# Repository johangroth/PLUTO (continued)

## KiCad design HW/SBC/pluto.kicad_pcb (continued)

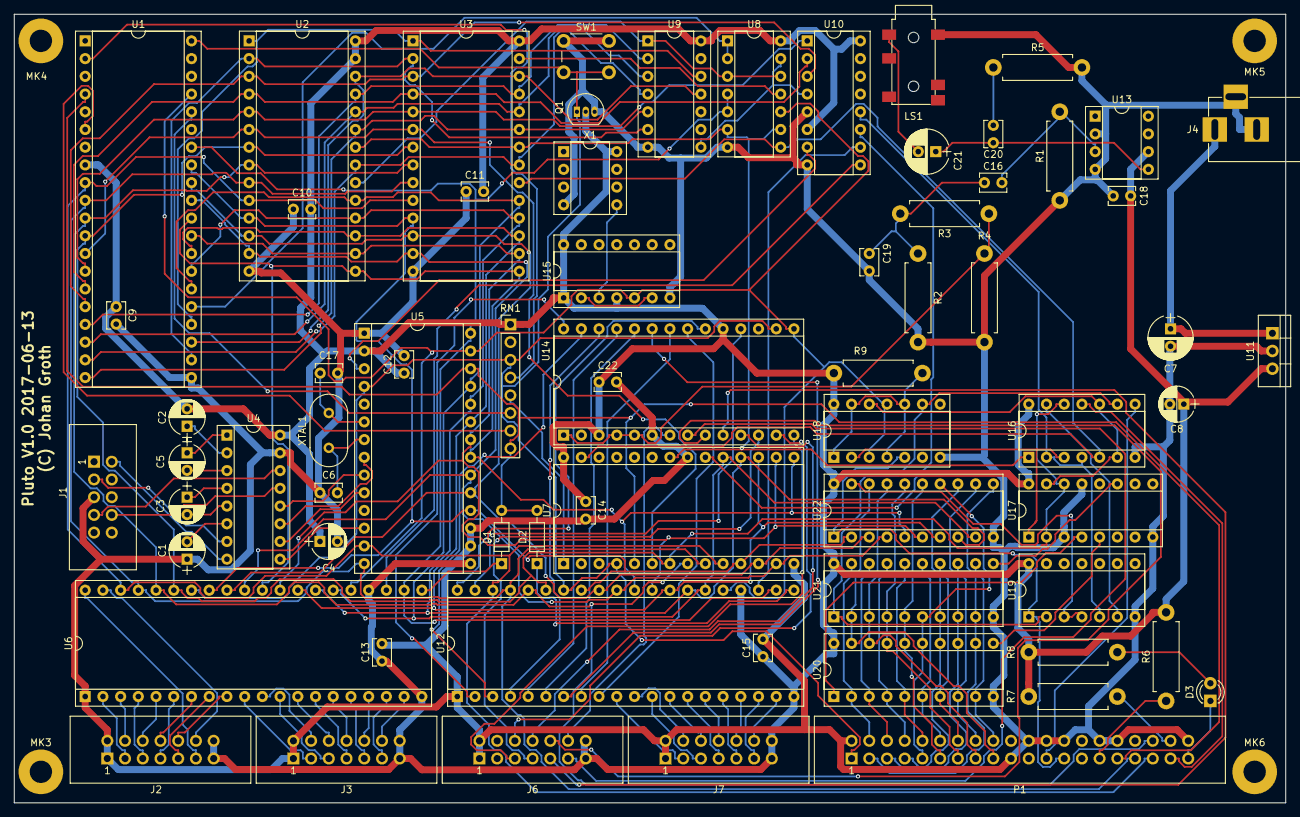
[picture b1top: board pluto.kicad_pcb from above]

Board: 2 copper layers, 182.2 x 113.0 mm, 73 parts (0 on the bottom side), 151 nets.

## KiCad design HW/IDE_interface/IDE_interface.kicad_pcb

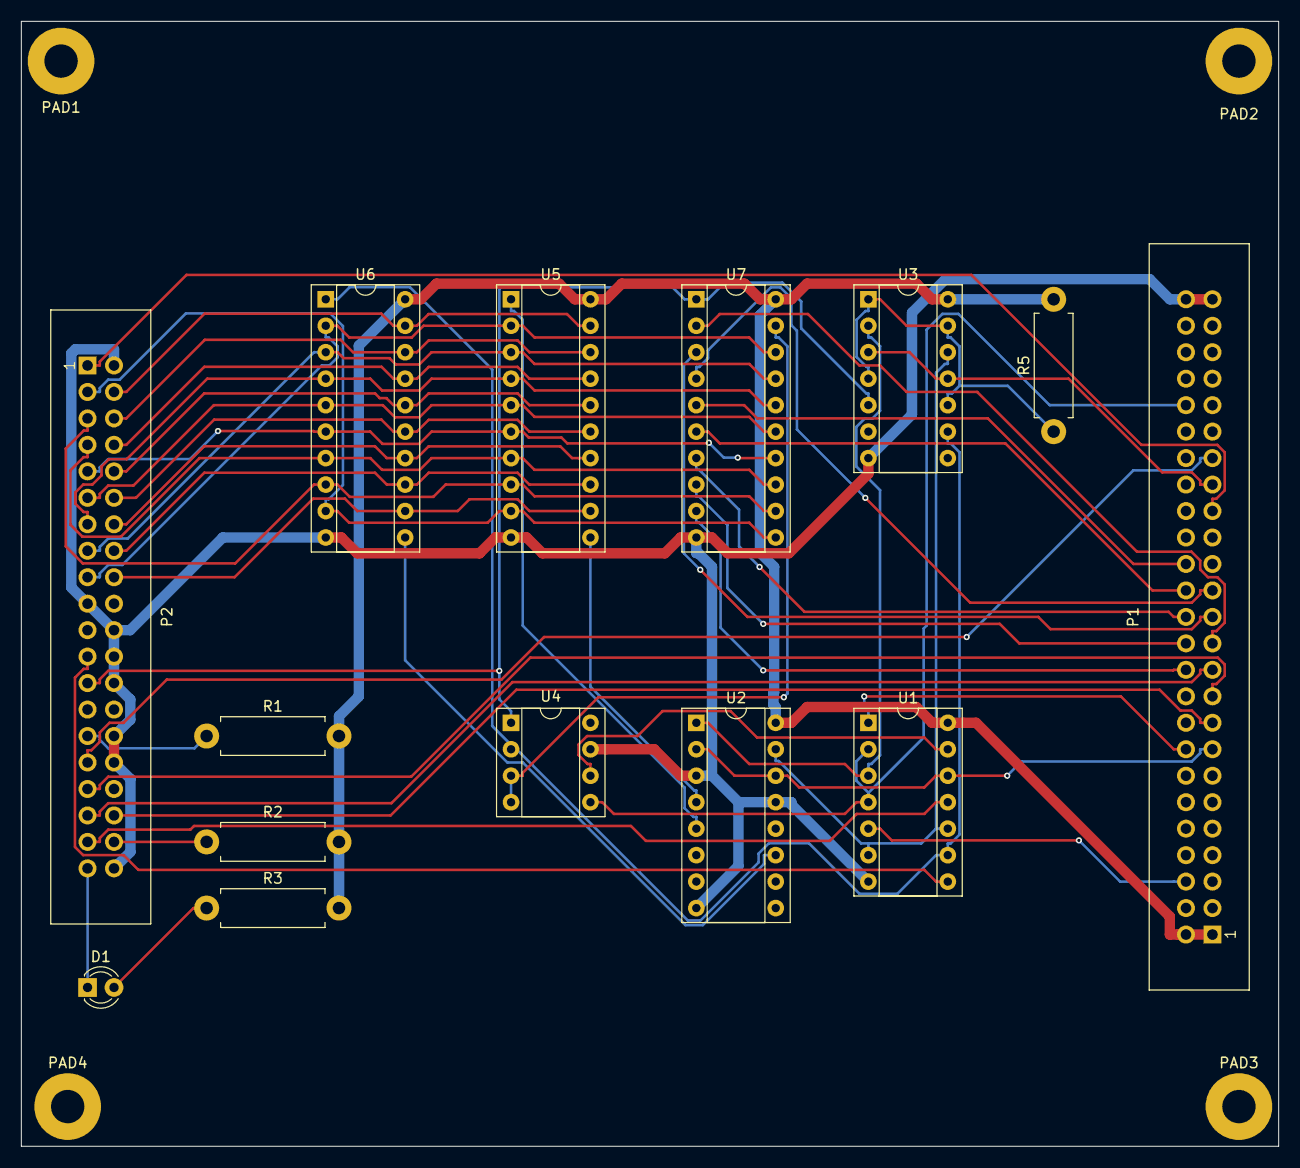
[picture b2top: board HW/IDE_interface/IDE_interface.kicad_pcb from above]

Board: 2 copper layers, 120.7 x 108.0 mm, 18 parts (0 on the bottom side), 52 nets.

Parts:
D1: LED; LED_D3.0mm
P1: EXPANSION PORT; IDC_Header_Straight_50pins
P2: IDE0; IDC_Header_Straight_40pins
PAD1, PAD2, PAD3, PAD4: MountingHole_3.2mm_M3_Pad
R1: 3.3K; R_Axial_DIN0411_L9.9mm_D3.6mm_P12.70mm_Horizontal
R2, R3: 1K; R_Axial_DIN0411_L9.9mm_D3.6mm_P12.70mm_Horizontal
R5: 1k; R_Axial_DIN0411_L9.9mm_D3.6mm_P12.70mm_Horizontal
U1: 74LS32; DIP-14_W7.62mm_Socket
U2: 74LS139; DIP-16_W7.62mm_Socket
U3: 74HC74; DIP-14_W7.62mm_Socket
U4: 74LS08; DIP-8_W7.62mm_Socket
U5, U6: 74LS574; DIP-20_W7.62mm_Socket
U7: 74HC245; DIP-20_W7.62mm_Socket

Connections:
/A0: P1.21, P2.35
/A1: P1.19, P2.33
/A2: P1.17, P2.36
/A3: P1.15, U1.12, U2.2, U2.14
/CLK2: P1.35, U3.3, U3.11
/D0: P1.23, U7.2
/D1: P1.25, U7.3
/D2: P1.27, U7.4
/D3: P1.30, U7.5
/D4: P1.28, U7.6
/D5: P1.26, U7.7
/D6: P1.24, U7.8
/D7: P1.22, U7.9
/IDE-D0: P2.17, U5.2, U6.2, U7.18
/IDE-D1: P2.15, U5.3, U6.3, U7.17
/IDE-D2: P2.13, U5.4, U6.4, U7.16
/IDE-D3: P2.11, U5.5, U6.5, U7.15
/IDE-D4: P2.9, U5.6, U6.6, U7.14
/IDE-D5: P2.7, U5.7, U6.7, U7.13
/IDE-D6: P2.5, U5.8, U6.8, U7.12
/IDE-D7: P2.3, U5.9, U6.9, U7.11
/IDE-D8: P2.4, U5.19, U6.19
/IDE-D9: P2.6, U5.18, U6.18
/IDE-D10: P2.8, U5.17, U6.17
/IDE-D11: P2.10, U5.16, U6.16
/IDE-D12: P2.12, U5.15, U6.15
/IDE-D13: P2.14, U5.14, U6.14
/IDE-D14: P2.16, U5.13, U6.13
/IDE-D15: P2.18, U5.12, U6.12
/~7F8X: P1.42, U1.2, U1.4, U4.5
/~DIOR: P2.25, U3.5, U4.1, U7.1
/~DIOW: P2.23, U1.8
/~IDE:CS0: P2.37, U1.11
/~IDE:CS1: P2.38, R2.1
/~IDE:DASP: D1.1, P2.39
/~IDE:DMACK: P2.29, R1.1
/~IRQ: P1.37, P2.31
/~MRD: P1.16, U1.1
/~MWR: P1.6, U1.5
/~RES: P1.33, P2.1
GND: P1.49, P1.50, P2.2, P2.19, P2.22, P2.24, P2.26, P2.30, P2.32, P2.40, U1.7, U2.3, U2.8, U2.13, U3.7, U4.7, U5.10, U6.10, U7.10
unnamed: D1.2, R3.1
unnamed: R5.1, U3.1, U3.4, U3.10, U3.13
unnamed: U1.3, U2.1, U3.2
unnamed: U1.9, U3.9, U4.2, U6.1
unnamed: U1.6, U1.10, U2.15, U3.12
unnamed: U1.13, U4.6
unnamed: U2.4, U5.11
unnamed: U2.5, U5.1
unnamed: U2.11, U6.11
unnamed: U4.3, U4.4, U7.19
VCC: P1.1, P1.2, R1.2, R2.2, R3.2, R5.2, U1.14, U2.16, U3.14, U5.20, U6.20, U7.20

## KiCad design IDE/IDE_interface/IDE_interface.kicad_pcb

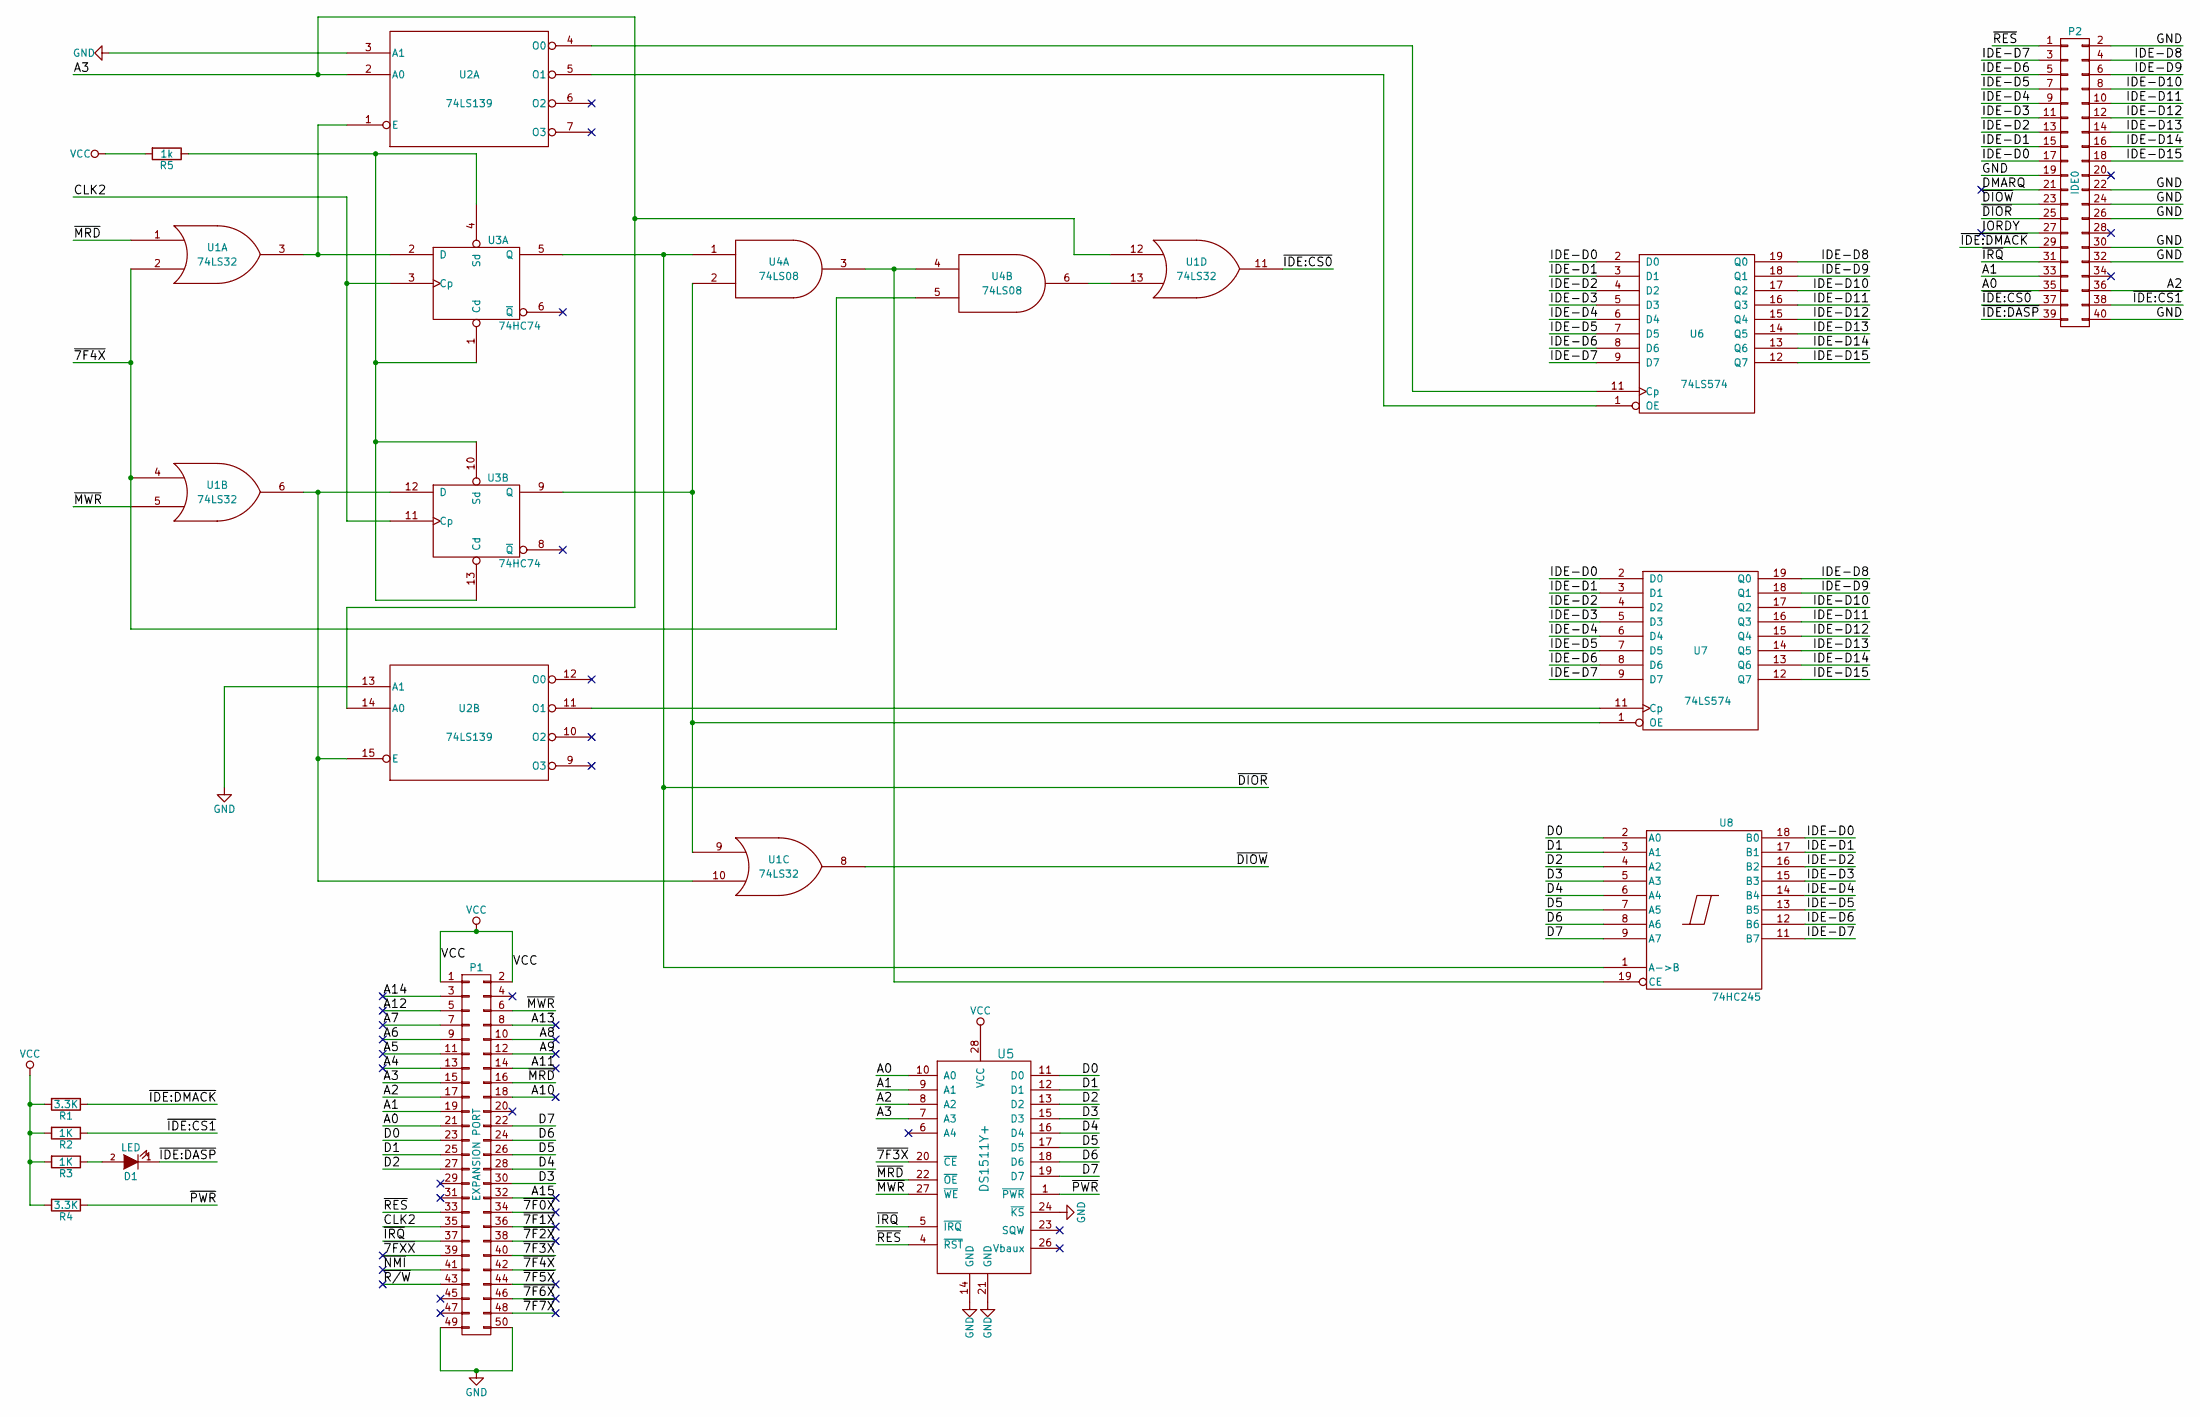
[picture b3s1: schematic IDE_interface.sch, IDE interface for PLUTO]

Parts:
D1: LED; LED-3MM
P1: EXPANSION PORT; Pin_Header_Straight_2x25
P2: IDE0; Pin_Header_Straight_2x20
R1, R4: 3.3K; Resistor_Horizontal_RM7mm
R2, R3: 1K; Resistor_Horizontal_RM7mm
R5: 1k; Resistor_Horizontal_RM7mm
U1: 74LS32; DIP-14_W7.62mm
U2: 74LS139; DIP-16_W7.62mm
U3: 74HC74; DIP-14_W7.62mm
U4: 74LS08; DIP-8_W7.62mm
U5: DS1511Y+; DIP-28_W15.24mm
U6, U7: 74LS574; DIP-20_W7.62mm
U8: 74HC245; DIP-20_W7.62mm

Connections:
/A0: P1.21, P2.35, U5.10 (A0)
/A1: P1.19, P2.33, U5.9 (A1)
/A2: P1.17, P2.36, U5.8 (A2)
/A3: P1.15, U1.12, U2.2 (A0), U2.14 (A0), U5.7 (A3)
/A4: P1.13
/A5: P1.11
/A6: P1.9
/A7: P1.7
/A8: P1.10
/A9: P1.12
/A10: P1.18
/A11: P1.14
/A12: P1.5
/A13: P1.8
/A14: P1.3
/A15: P1.32
/CLK2: P1.35, U3.3 (Cp), U3.11 (Cp)
/D0: P1.23, U5.11 (D0), U8.2 (A0)
/D1: P1.25, U5.12 (D1), U8.3 (A1)
/D2: P1.27, U5.13 (D2), U8.4 (A2)
/D3: P1.30, U5.15 (D3), U8.5 (A3)
/D4: P1.28, U5.16 (D4), U8.6 (A4)
/D5: P1.26, U5.17 (D5), U8.7 (A5)
/D6: P1.24, U5.18 (D6), U8.8 (A6)
/D7: P1.22, U5.19 (D7), U8.9 (A7)
/DMARQ: P2.21
/IDE-D0: P2.17, U6.2 (D0), U7.2 (D0), U8.18 (B0)
/IDE-D1: P2.15, U6.3 (D1), U7.3 (D1), U8.17 (B1)
/IDE-D2: P2.13, U6.4 (D2), U7.4 (D2), U8.16 (B2)
/IDE-D3: P2.11, U6.5 (D3), U7.5 (D3), U8.15 (B3)
/IDE-D4: P2.9, U6.6 (D4), U7.6 (D4), U8.14 (B4)
/IDE-D5: P2.7, U6.7 (D5), U7.7 (D5), U8.13 (B5)
/IDE-D6: P2.5, U6.8 (D6), U7.8 (D6), U8.12 (B6)
/IDE-D7: P2.3, U6.9 (D7), U7.9 (D7), U8.11 (B7)
/IDE-D8: P2.4, U6.19 (Q0), U7.19 (Q0)
/IDE-D9: P2.6, U6.18 (Q1), U7.18 (Q1)
/IDE-D10: P2.8, U6.17 (Q2), U7.17 (Q2)
/IDE-D11: P2.10, U6.16 (Q3), U7.16 (Q3)
/IDE-D12: P2.12, U6.15 (Q4), U7.15 (Q4)
/IDE-D13: P2.14, U6.14 (Q5), U7.14 (Q5)
/IDE-D14: P2.16, U6.13 (Q6), U7.13 (Q6)
/IDE-D15: P2.18, U6.12 (Q7), U7.12 (Q7)
/IORDY: P2.27
/~7F0X: P1.34
/~7F1X: P1.36
/~7F2X: P1.38
/~7F3X: P1.40, U5.20 (~CE)
/~7F4X: P1.42, U1.2, U1.4, U4.5
/~7F5X: P1.44
/~7F6X: P1.46
/~7F7X: P1.48
/~7FXX: P1.39
/~DIOR: P2.25, U3.5 (Q), U4.1, U8.1 (A->B)
/~DIOW: P2.23, U1.8
/~IDE:CS0: P2.37, U1.11
/~IDE:CS1: P2.38, R2.1
/~IDE:DASP: D1.1 (K), P2.39
/~IDE:DMACK: P2.29, R1.1
/~IRQ: P1.37, P2.31, U5.5 (~IRQ)
/~MRD: P1.16, U1.1, U5.22 (~OE)
/~MWR: P1.6, U1.5, U5.27 (~WE)
/~NMI: P1.41
/~PWR: R4.1, U5.1 (~PWR)
/~R/W: P1.43
/~RES: P1.33, P2.1, U5.4 (~RST)
GND: P1.49, P1.50, P2.2, P2.19, P2.22, P2.24, P2.26, P2.30, P2.32, P2.40, U1.7 (GND), U2.3 (A1), U2.8 (GND), U2.13 (A1), U3.7 (GND), U4.7 (GND), U5.14 (GND), U5.21 (GND), U5.24 (~KS), U6.10 (GND), U7.10 (GND), U8.10 (GND)
unnamed: D1.2 (A), R3.1
unnamed: R5.1, U3.1 (Cd), U3.4 (Sd), U3.10 (Sd), U3.13 (Cd)
unnamed: U1.3, U2.1 (E), U3.2 (D)
unnamed: U1.9, U3.9 (Q), U4.2, U7.1 (OE)
unnamed: U1.6, U1.10, U2.15 (E), U3.12 (D)
unnamed: U1.13, U4.6
unnamed: U2.4 (O0), U6.11 (Cp)
unnamed: U2.5 (O1), U6.1 (OE)
unnamed: U2.11 (O1), U7.11 (Cp)
unnamed: U4.3, U4.4, U8.19 (CE)
VCC: P1.1, P1.2, R1.2, R2.2, R3.2, R4.2, R5.2, U1.14 (VCC), U2.16 (VCC), U3.14 (VCC), U5.28 (VCC), U6.20 (VCC), U7.20 (VCC), U8.20 (VCC)

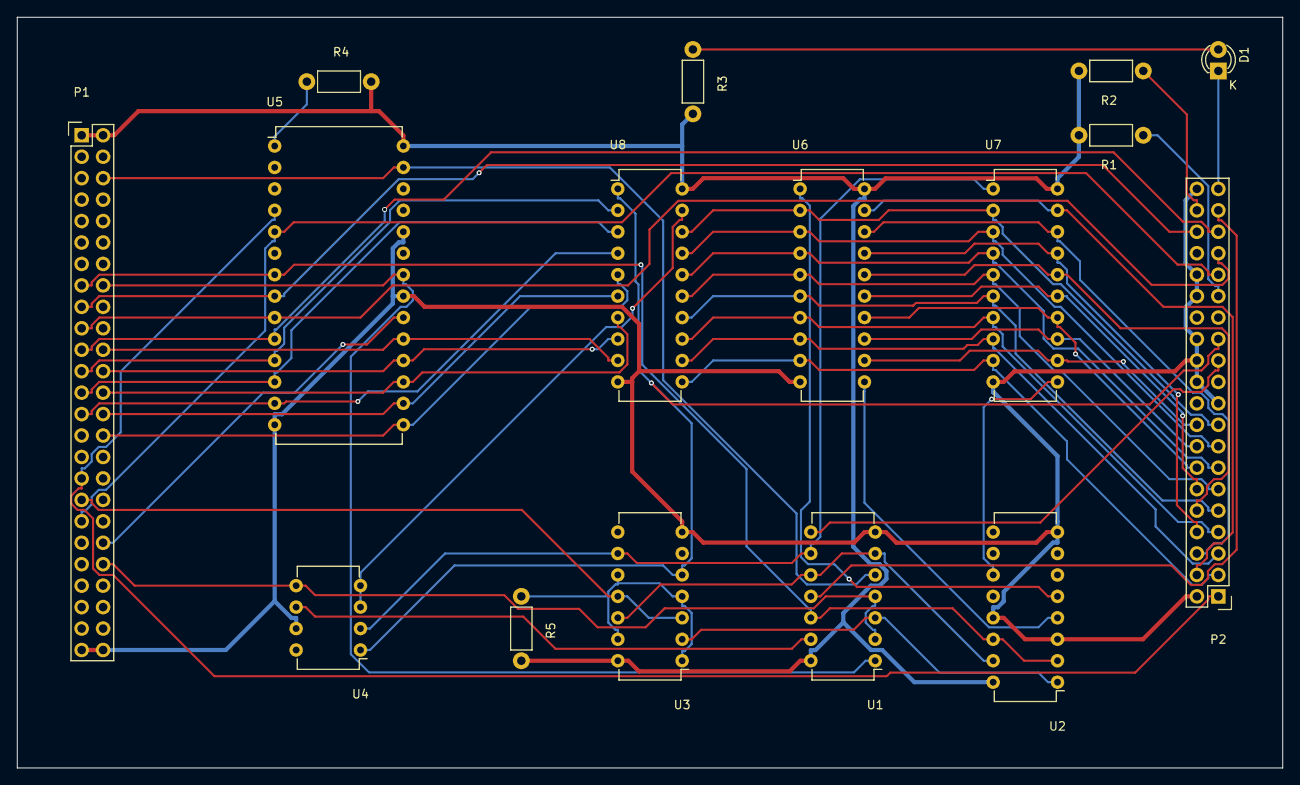
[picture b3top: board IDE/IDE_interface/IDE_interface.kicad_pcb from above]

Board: 2 copper layers, 149.9 x 88.9 mm, 16 parts (0 on the bottom side), 54 nets.

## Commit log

2016-09-28 Updated PROMPT to handle large messages.
2016-09-29 Added a lot of documentation
2016-09-29 Minor updates to docs.
2016-09-29 Correction of spelling mistakes, wording etc
2016-10-01 Updates to goals
2016-10-07 Added datasheets for IDE interface. TaliForth source added. KiCad documentation added. Some ide assembler routines added (not tested). VT100 escape sequences added.
2016-10-12 Added escape seq for colours. Adjusted ram size for Tali Forth
2016-10-27 Removed hardcoded addresses to subroutines printed out by Q command. Added prototype for an IDE driver. Added datasheets for RTC.
2016-11-21 Use 65C20 mnemonics
2016-12-04 Added datasheet for CDP 65C51.
2016-12-04 Corrected spelling mistakes.
2016-12-08 Added Daryl Rictor's XModem implementation instead of SyMonIII upload/download subroutines.
2016-12-08 Using SyMonIII subroutines in xmodem.asm.
2016-12-12 Integration of XMODEM/CRC with SyMonIII
2017-02-14 New version of Tali Forth
2017-02-14 Added TaliForth
2017-02-14 Added IDE interface schema
2017-02-15 Initialisation of VIA. Added emacs TAGS to SyMonIII.
2017-02-15 remove never used schematics.
2017-02-15 Deleted TaliForth
2017-02-15 Added TaliForth without .git directory
2017-02-18 Move ide routines to SyMonII. Small updates to xmodem. Tagged all asm files.
2017-02-18 Added TAGS to Tali Forth. Small updates to xmodem.asm
2017-02-21 Moved all assembler files to one directory.
2017-02-21 Tali kernel removed from assembly chain.
2017-02-21 Beginning of a init routine for IDE.
2017-02-22 Removed seldom used commands in kernel. Clean up of Forth.
2017-02-22 Added cfs documentation.
2017-02-22 Indentation changes.
2017-02-22 CFS documentation. Perhaps move to its own file.
2017-02-22 All available CFS documentation added.
2017-02-23 Finished doc for CFS.
2017-02-23 Basic ide has two ZP var d and e. Hangover from Z-80 port. Check original what is going on there. cfs calls read sector as a test. Main calls cfs as a test.
2017-02-23 Cleanup of comments in cfs.asm. Started a Zero Page variable list for use of all asm files.
2017-02-24 Updates tags files. Embroy to Makefile added.
2017-02-26 Added forth vi and asm from Durexforth.
2017-02-26 chmodded vi.fs
2017-03-07 Removed TaliForth
2017-03-14 vt100 control sequences.
2017-03-23 Revised the memory map. I/O blocks are now 32 bytes.
2017-03-23 Updates to IDE interface.
2017-03-23 Added vt100 terminal code and schematics for PLUTO SBC board.
2017-03-24 Changed names of IO select lines.
2017-03-24 Renamed IDE directory to HW
2017-03-24 Started to make the schematics for pluto main board using multiple sheets.
2017-03-25 PLUTO SBC with RTC schematics done.
2017-03-25 Via connectors.pro? Commited and pushed just in case.
2017-03-25 The PCB layout editor doesn't like 7805's footprint.
2017-03-25 Removed old Pluto schematics.
2017-03-25 Renamed multisheet schematics to SBC
2017-03-26 Some changes to the schematics.
2017-03-27 Updated test with new address for VIA. Updated doc with VIA details.
2017-03-28 Added a couple of procedure assembler directives. ctags file added
2017-03-28 Connected all relevant I/O select signals to expansion port.
2017-03-29 Corrected some Z80 -> 65C02 errors.
2017-03-29 Added some comments.
2017-03-29 New indentaion.
2017-03-30 Removed duplicated options in asmpluto.sh.
2017-03-31 Downloaded the orginal version of SyMonIII.
2017-03-31 Removed Tali Forth as it is going to be rewritten when Liara Forth is in Beta.
2017-04-03 New MB design. Includes RTC. New IDE design.
2017-04-04 Added DS1511 code. Code in 65816 assembler so conversion is needed.
2017-04-19 Added original xmodem code some datasheets and a C02Monitor.
2017-04-19 Fixed pluto kernel (SyMon, command address table had been corrupted).
2017-04-20 Tab clean up. Rewrite of Flush in xmodem.asm.
2017-04-20 Include xmodem in the assembly list.
2017-04-25 Removed xmodem from main.asm. Xmodem seem to disrupt serial communication. Disabled upload/download in kernel.
2017-04-25 Ignore .rom files. Original SyMonIII's tags file is added.
2017-04-29 Updates to pcb and monitor.
2017-04-29 Move dicoupling capacitators as close the chips as possible.
2017-05-04 Added bin to hex util
2017-05-04 Schema changes to SBC
2017-05-05 Initialise VIA properly.
2017-05-05 BinToHex added. Updates to SBC schema. Added ISR for VIA (still WIP).
2017-05-05 Updates to tags with new files.
2017-05-08 Refactored VIA and ISR code.
2017-05-08 Improved VIA interrupt handling. Input of address is broken.
2017-05-09 updated tags
2017-05-09 Interrupt vector is stored in bash302 and ISR has been updated accordingly.
2017-05-10 Begun to add VIA interrupt code. Some formatting of comments.
2017-05-10 Added acia.asm. Guarded interrupt vector setup with sei/cli.
2017-05-10 Added partial handling of VIA in ISR.
2017-05-10 Trying to fix BRK ISR after code review by BigDumbDinosaur.
2017-05-10 More improvements to ISR. xmodem doesn't handle download anymore.
2017-05-10 Fixed merge errors.
2017-05-10 Removed obsolete code.
2017-05-10 Download works. test program works.
2017-05-15 New board layout. WIP
2017-05-15 Rewrite of ISR.
2017-05-16 Monitor now in a state where you can develeop code and put it in RAM.
2017-05-16 Test program reads the RTC.
2017-05-16 Conversion of DS1511 BCD date values to CFS compact format. Still WIP.
2017-05-16 Added a utils class (BCD->BIN, BIN->BCD so far).
2017-05-19 Updated pluto bios/monitor to not wipe > F00. RTC got wiped.
2017-05-22 PUT, GET and PRINT_DATE_AND_TIME works. PUT has no input routine yet.
2017-05-24 asm4doxy and assembler book.
2017-05-24 assembler book added.
2017-05-24 New SBC PCB. Started to split pluto_kernel.asm into bios, monitor and miniassembler/disassembler. Various other updates.
2017-05-24 Removed docs not important to project.
2017-05-24 Removed KiCad documentation
2017-05-30 New board layout with decoupling caps in the right place. Updates to the RTC code (IRQ still doesn't work).
2017-05-30 WIP, write an ISR that updates console TOD every 500ms.
2017-06-03 New schema. Adding a VIA and sound chip.
2017-06-03 Moved IDE schematics (WIP) into pluto.
2017-06-03 Added IDE interface to PLUTO board.
2017-06-06 Connected most hierarchical labels between the sheets. Added a connector to AY IO port.
2017-06-07 Still no VCC net in PCBnew.
2017-06-08 New PCB layout. Added datasheet for AY-3-8912 and LM386.
2017-06-12 Autorouted PCB.
2017-06-13 Added some silk screen text.
2017-06-16 Moved seldom used files to WIP. Added C02BIOS. Added gerbers for new PCB (sent to manufacturer).
2017-07-03 Schema is now Alpha.
2017-07-04 Added makefile for WIP files.
2017-07-05 Reorganised directory
2017-07-05 Reorganised directories
2017-07-06 Made sure all the not used flip's input pins are grounded. Added original z80 ide code. Cosmetic changes to ide routine.
2017-07-06 Started to write initialisation for own bios.
2017-07-10 Added path to 65xx library
2017-07-10 Initialised the irq soft vector table.
2017-07-10 Added ISR soft vector table initialisation.
2017-07-10 File name change
2017-07-10 Initialisation routines developed. New library preferences to KiCad schema. Broken though but it doesn't matter as the PCB has been manufactured. Schema and PCB doesn't match 100% (e.g. 74HCT74 unuse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
2017-07-10 Lots of refactoring. Initialisation of HW is done.
2017-07-11 Break interrupt service routine done.
2017-07-18 Made sure via1 delay routine works.
2017-08-09 Small changes to schematics. Futher development of BIOS.
2017-08-15 Update of test program to test both VIA.
2017-08-15 Use correct assembler flags for Pluto bios. Deleted redundant include file. Minor changes to bios.asm.
2017-08-15 Removed bios_include.inc
2017-08-15 Made code a bit more readable.
2017-08-16 ACIA ISR and input/output buffer handling added.
2017-08-16 Missing label in bios.asm. Hi low pointer reversed in zp.inc.
2017-08-17 Got hello world working with transmit IRQ. Nested IRQ ISR re-enabled.
2017-08-17 All labels must end with : for colour coding to work.
2017-08-18 Got interrupt driven transmission working again (right command register bit pattern helps). Started making screen manipulation routines.
2017-08-21 Added all support VT100 ANSI escape sequences supported by ASCII Video Terminal. Implemented prout.
2017-08-21 Added all support VT100 ANSI escape sequences supported by ASCII Video Terminal.
2017-08-21 More screen routines made.
2017-08-22 Added read_line et al.
2017-08-23 Fixed bug in backspace proc.
2017-08-23 Changed a comment.
2017-08-24 Added display_hex subroutine.
2017-08-24 Implemented suppression of leading zeroes in hex_to_ascii.
2017-08-30 Added beginning of input hex subroutine.
2017-08-30 read_line can read hex input. input_hex is WIP.
2017-09-12 Added input_buffer_to_binary (WIP).
2017-09-21 Input hex routine is working now.
2017-09-21 Started an decimal input routine. Added ASCII->bin and bin->ASCII routines. Written by BDD (6502.org).
2017-09-21 Removed old ascii -> bin
2017-09-21 Reindented ascii_to_bin.asm
2017-09-21 Reindented bin_to_ascii.asm
2017-09-26 Use the --nostart flag so the binary doesn't contain start address. It will also make the binary 32KiB instead 64KiB
2017-10-11 Made the list file easier to read in text editor.
2017-10-18 Small formatting changes.
2017-10-27 Removed redundant code.
2017-11-02 Added ide routines. Small refactoring.
2017-11-02 Include ide_routines.asm when assembling pluto rom file.
2017-11-21 Fixed prout so it can print string longer than 256 bytes. Changed added comments here and there.
2017-11-21 Fixed indentation and added some comments.
2017-11-21 Fixed indentation and added some comments again.
2017-11-21 Removed an unused proc.
2017-12-11 Small changes to comments.
2017-12-19 Added comments.
2017-12-25 Some small changes to the input routines.
2017-12-25 Changed all TTLs to HC family.
2018-01-07 Using ascii_to_bin but there is a bug. ABC gets converted to CBC, ie last character becomes the first character.
2018-01-10 Input/Output of numbers done.
2018-01-11 Made chin and chout a bit more efficient. Added chin_no_wait for use with xmodem transfer.
2018-01-11 Started to use control_flags for handling radix. WIP. Evaluate radix must be updated.
2018-01-11 Cleaned up bin_to_ascii. Only tested dec input to hex output.
2018-01-12 Converted code to lower case.
2018-01-12 Indented code with 6510i.pl
2018-01-12 Comparison between facbcd and binbcd32.
2018-01-13 Start of the PLUTO monitor.
2018-01-13 Started to move VIA ISR to via.asm
2018-01-13 Sorted comments.
2018-01-13 Include all assembler files in the make file.
2018-01-14 Started to implement [D] command.
2018-01-14 Dump command implementation is progressing.
2018-01-15 Added ZP variables for holding address
2018-01-15 Use address_low/high instead of index_low/high.
2018-01-15 New tags
2018-01-16 Dump command completed.
2018-01-16 Added fill command and download with XMODEM/CRC.
2018-01-17 Added upload with XMODEM/CRC.
2018-01-18 Fixed bug in fill subroutine.
2018-01-20 Display of date and time done. Set date and time still WIP.
2018-01-20 tags changes
2018-01-22 Input day of week proc nearly done.
2018-02-06 input_day_of_week development (WIP).
2018-04-14 Progress with set time/date
2018-04-14 Beginning of rewrite of input of day of week.
2018-04-20 Deleted old/obsolete files.
2018-04-20 Restructed project
2018-05-12 Input of day works.
2018-05-12 Input of day of month, month works. Validation of year doesn't.
2018-05-12 Set date seems to work OK. No validation though.
2018-05-13 More comments.
2018-05-13 tags
2018-05-17 Saved a byte by changing jsr/rts to jmp.
2018-06-21 Added source file for SC28L92 DUART.
2018-06-21 Some dummy procs for SC28L92.
2019-07-06 Added dis-assembler. Removed files that was never needed. Updates to schematics files due to upgrade to KiCad 5.1.
2019-07-07 Added some decimal output routines. Fixed tags files and removed ctags (atom handles tags itself). Some documentation updates.
